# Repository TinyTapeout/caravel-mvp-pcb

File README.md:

# Caravel MVP

This is a sample "minimum viable PCB" for [Caravel chips](https://caravel-harness.readthedocs.io/en/latest/): Google MPW or [chipIgnite](https://info.efabless.com/chipignite-v2), including variants for [TinyTapeout](https://tinytapeout.com/).

Fork this repo to get a head start on spinning your own Caravel based PCB.

The circuit includes all the critical (required) elements, basically:

  * power regulation;
  * a clock signal;
  * flash memory, for code; and
  * the chip itself

along with basic passive support (bypass caps...) [Full schematic PDF here](doc/caravel-mvp.pdf)

It also has a few switches and connectors, as demonstrations.  These are enclosed in dotted boxes to highlight their optionality.

The full schematic is available as a PDF in the doc/ directory.

A sample layout was also included, though routing was not completed as you're certainly going to want to change components and floorplan around for your custom boards.

# Footprints and Symbols

Useful symbols and footprints are used here and elsewhere, included as a submodule.

```
  git submodule update --init --recursive
```
will actually brings these in to your local fs.

# TinyTapeout

A TinyTapeout-specific versions are also included. If using along with the Caravel CPU, the only real differences are in the symbol and net names used, as this helps to clarify things a lot.

However, you may also use it stand-alone, in which case a few components aren't required (e.g. flash memory) and a few additional ones are needed (mainly passives for pull-ups and config bootstraps).

If you are implementing a PCB for a TinyTapeout chip, simply:

```
  git checkout tt123
```

and the schematic ([TT version PDF here](doc/caravel-mvp-tinytapeout.pdf)) will include something like this instead:

along with the TT standalone config sheet.

# Resources

### TinyTapeout
[TinyTapeout](https://tinytapeout.com/) is an educational project that makes it easier and cheaper than ever to get your digital designs manufactured on a real chip.

It's the easiest and cheapest way I know to get your designs on an ASIC.

### Caravel

Caravel is composed of a harness frame plus two wrappers for drop-in modules for the management area and user project area.  Basically a SoC with a RISC-V CPU, space for user designs and ways to connect those to the outside world.

See:
 * [Caravel chips](https://caravel-harness.readthedocs.io/en/latest/)
 * [efabless/caravel](https://github.com/efabless/caravel)
 * [efabless/caravel_mgmt_soc_litex](https://github.com/efabless/caravel_mgmt_soc_litex)

# License

This is meant as a template and starting point for your own projects and is all released under as open hardware.  The MVP schematics and layouts are

  Copyright (C) 2023 Pat Deegan, [Psychogenic Technologies](https://psychogenic.com)

and released under the terms of the Apache License, version 2.0.  See the accompanying LICENSE file for details.

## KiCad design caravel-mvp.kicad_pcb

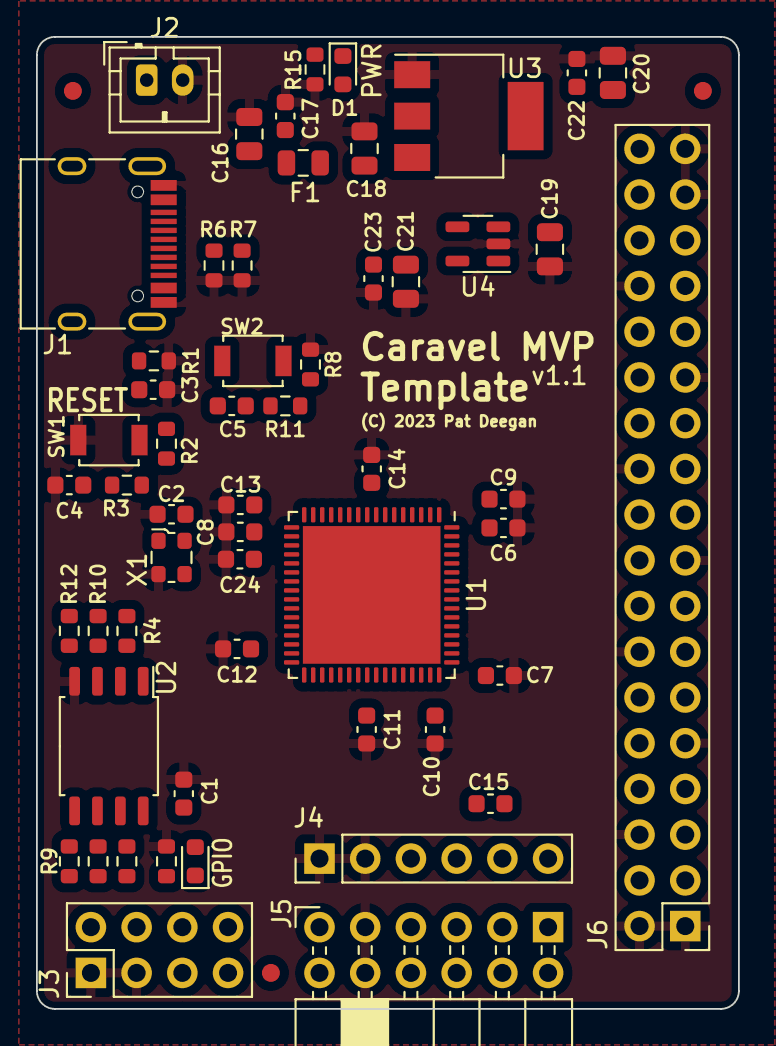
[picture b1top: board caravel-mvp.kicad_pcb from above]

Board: 4 copper layers, 39.0 x 54.0 mm, 58 parts (0 on the bottom side), 59 nets, no tracks yet.

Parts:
C1, C2, C6, C7, C8, C9, C10, C11, C12, C13, C14, C15, C17, C22, C23: 100nF; C_0603_1608Metric
C3: 6800pF; C_0603_1608Metric
C4, C5, C24: 1uF; C_0603_1608Metric
C16, C18, C19, C21: 10uF; C_0805_2012Metric
C20: 22uF; C_0805_2012Metric
D1, D2: LED; LED_0603_1608Metric
F1: 350mA; Fuse_0805_2012Metric
FID1, FID2, FID3: Fiducial; Fiducial_1mm_Mask2mm
J1: USB_C_Receptacle_USB2.0; USB_C_Receptacle_HRO_TYPE-C-31-M-12
J2: Conn_01x02; JST_PH_B2B-PH-K_1x02_P2.00mm_Vertical
J3: Conn_02x04_Odd_Even; PinHeader_2x04_P2.54mm_Vertical
J4: Conn_01x06; PinHeader_1x06_P2.54mm_Vertical
J5: 613012243121; PinSocket_2x06_P2.54mm_PMODHost1A
J6: Conn_02x18_Odd_Even; PinHeader_2x18_P2.54mm_Vertical
R1: 1M; R_0603_1608Metric
R2, R4, R5, R8, R9, R10, R12, R13: 10k; R_0603_1608Metric
R3, R6, R7, R11: 5.1k; R_0603_1608Metric
R14, R15: 510; R_0603_1608Metric
SW1, SW2: B3U-1000P; SW_SPST_B3U-1000P
U1: Caravel_QFN_TT3; QFN-64-1EP_9x9mm_P0.5mm_EP7.65x7.65mm
U2: W25Q32JVSS; SOIC-8_5.23x5.23mm_P1.27mm
U3: AZ1117-3.3; SOT-223-3_TabPin2
U4: AP2112K-1.8; SOT-23-5
X1: 10MHz; Oscillator_SMD_ECS_2520MV-xxx-xx-4Pin_2.5x2.0mm

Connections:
+1V8: C6.1, C7.2, C8.1, C21.1, C23.1, U1.18 (vccd), U1.49 (vccd1), U1.63 (vccd2), U4.5 (VOUT)
+3V3: C1.1, C2.2, C5.1, C9.2, C10.1, C11.1, C12.1, C13.1, C14.2, C19.1, C20.1, C22.1, C24.1, D1.2 (A), J3.7, J4.3, J5.6 (VCC), J5.12 (VCC), J6.34, J6.36, R2.1, R4.1, R5.1, R9.1, R10.1, R12.2, R13.2, SW2.2, U1.9 (vdda2), U1.17 (vddio), U1.30 (vdda), U1.40 (vdda1), U1.47 (vdda1), U1.64 (vddio), U2.8 (VCC), U3.2 (VO), U4.1 (VIN), U4.3 (EN), X1.4 (VDD)
+5V: C18.1, F1.2, U3.3 (VI)
/SCS.DRV_{0}: J6.24, U1.42 (driver_sel0/crvio[8])
/SCS.DRV_{1}: J6.26, U1.43 (driver_sel1/crvio[9])
/SCS.setdiv: C24.2, J6.32
/in0: J6.2, U1.59 (in[0]/crvio[21])
/in1: J6.4, U1.60 (in[1]/crvio[22])
/in2: J6.8, U1.61 (in[2]/crvio[23])
/in3: J6.10, U1.62 (in[3]/crvio[24])
/in4: J6.12, U1.2 (in[4]/crvio[25])
/in5: J6.16, U1.3 (in[5]/crvio[26])
/in6: J6.18, U1.4 (in[6]/crvio[27])
/in7: J6.20, U1.5 (in[7]/crvio[28])
/out0: J5.1 (IO1), U1.6 (out[0]/crvio[29])
/out1: J5.2 (IO2), U1.7 (out[1]/crvio[30])
/out2: J5.3 (IO3), U1.8 (out[2]/crvio[31])
/out3: J5.4 (IO4), U1.11 (out[3]/crvio[32])
/out4: J5.7 (IO5), U1.12 (out[4]/crvio[33])
/out5: J5.8 (IO6), U1.13 (out[5]/crvio[34])
/out6: J5.9 (IO7), U1.14 (out[6]/crvio[35])
/out7: J5.10 (IO8), U1.15 (out[7]/crvio[36])
/prj_io37: C5.2, R11.2
/ready: J6.31, U1.16 (ready/crvio[37])
/sel0: J6.3, U1.46 (sel[0]/crvio[12])
/sel1: J6.5, U1.48 (sel[1]/crvio[13])
/sel2: J6.7, U1.50 (sel[2]/crvio[14])
/sel3: J6.11, U1.51 (sel[3]/crvio[15])
/sel4: J6.13, U1.53 (sel[4]/crvio[16])
/sel5: J6.15, U1.54 (sel[5]/crvio[17])
/sel6: J6.19, U1.55 (sel[6]/crvio[18])
/sel7: J6.21, U1.57 (sel[7]/crvio[19])
/sel8: J6.23, U1.58 (sel[8]/crvio[20])
GND: C1.2, C2.1, C3.2, C4.2, C6.2, C7.1, C8.2, C9.1, C10.2, C11.2, C12.2, C13.2, C14.1, C16.2, C17.2, C18.2, C19.2, C20.2, C21.2, C22.2, C23.2, J1.A1 (GND), J1.A12 (GND), J1.B1 (GND), J1.B12 (GND), J2.2, J3.1, J3.3, J4.1, J4.2, J5.5 (GND), J5.11 (GND), J6.1, J6.6, J6.9, J6.14, J6.17, J6.22, J6.25, J6.30, J6.33, J6.35, R1.2, R6.2, R7.2, R8.2, R14.2, R15.2, SW1.1, U1.1 (vssa2), U1.10 (vssd2), U1.20 (vssa), U1.23 (vssd), U1.29 (vssio), U1.38 (vssa1), U1.39 (vssd1), U1.52 (vssa1), U1.56 (vssio), U1.65 (ThermalPad), U2.4 (GND), U3.1 (GND), U4.2 (GND), X1.2 (GND)
HK_CSB: J3.4, U1.34 (crvio[3]_CSB)
HK_JTAG: J3.2, U1.31 (crvio[0]_JTAG)
HK_SCK: J3.6, U1.35 (crvio[4]_SCK)
HK_SDI: J3.8, U1.33 (crvio[2]_SDI)
HK_SDO: J3.5, U1.32 (crvio[1]_SDO)
unnamed: D1.1 (K), R15.1
unnamed: D2.1 (K), R14.1
unnamed: J1.A5 (CC1), R7.1
unnamed: J1.B5 (CC2), R6.1
unnamed: C3.1, J1.S1 (SHIELD), R1.1
unnamed: C15.1, J4.6
unnamed: R2.2, R3.1, SW1.2
unnamed: R8.1, R11.1, SW2.1
unnamed: R12.1, U2.3 (IO2)
unnamed: R13.1, U2.7 (IO3)
VBUS: C16.1, C17.1, F1.1, J1.A4 (VBUS), J1.A9 (VBUS), J1.B4 (VBUS), J1.B9 (VBUS), J2.1
flash_clk: R5.2, U1.25 (flash_clk), U2.6 (CLK)
flash_csb: R4.2, U1.24 (flash_csb), U2.1 (~CS)
flash_io0: R9.2, U1.26 (flash_io0), U2.5 (DI(IO0))
flash_io1: R10.2, U1.27 (flash_io1), U2.2 (DO(IO1))
gpio: D2.2 (A), U1.28 (gpio)
osc_out: U1.22 (clock), X1.3 (OUT)
ser_rx: J4.4, J6.29, U1.36 (crvio[5]_ser_rx)
ser_tx: J4.5, J6.27, U1.37 (crvio[6]_ser_tx)
~SOC_RST: C4.1, C15.2, R3.2, U1.21 (resetb)

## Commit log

2023-10-24 Create LICENSE
2023-10-24 Caravel MVPCB initial commit
2023-10-24 TinyTapeout 1-2-3 version
2023-10-24 Tinytapeout branch docs
2023-10-24 img url fix
2023-10-24 Link to PDF schem
2023-10-24 Link fix ugh
2023-10-24 Link to TT variant PDF schem
2023-10-24 TinyTapeout Stand-alone (no CPU) circuit and info
2023-10-24 Updated main readme and tt version doc
2023-10-24 Friendlier sort of scan drive bits, and more doc
2023-10-25 Reset risetime fix
2023-10-25 Updated PDF
2023-10-25 re-arranging, space for reset
2023-10-25 Reset rise and slow clock config fixes
2023-10-25 update TT variant schem
2023-10-27 Commenting and colour adjustments
2023-10-27 Comment clarifications
2023-10-27 Updated readme and schem PDF
2023-10-27 TT variant schem PDF update
2023-10-27 symbol submodule loading directives
2023-10-27 minor cleanups and clarifications
2023-10-27 Cleanups and even more clarifications in comments
